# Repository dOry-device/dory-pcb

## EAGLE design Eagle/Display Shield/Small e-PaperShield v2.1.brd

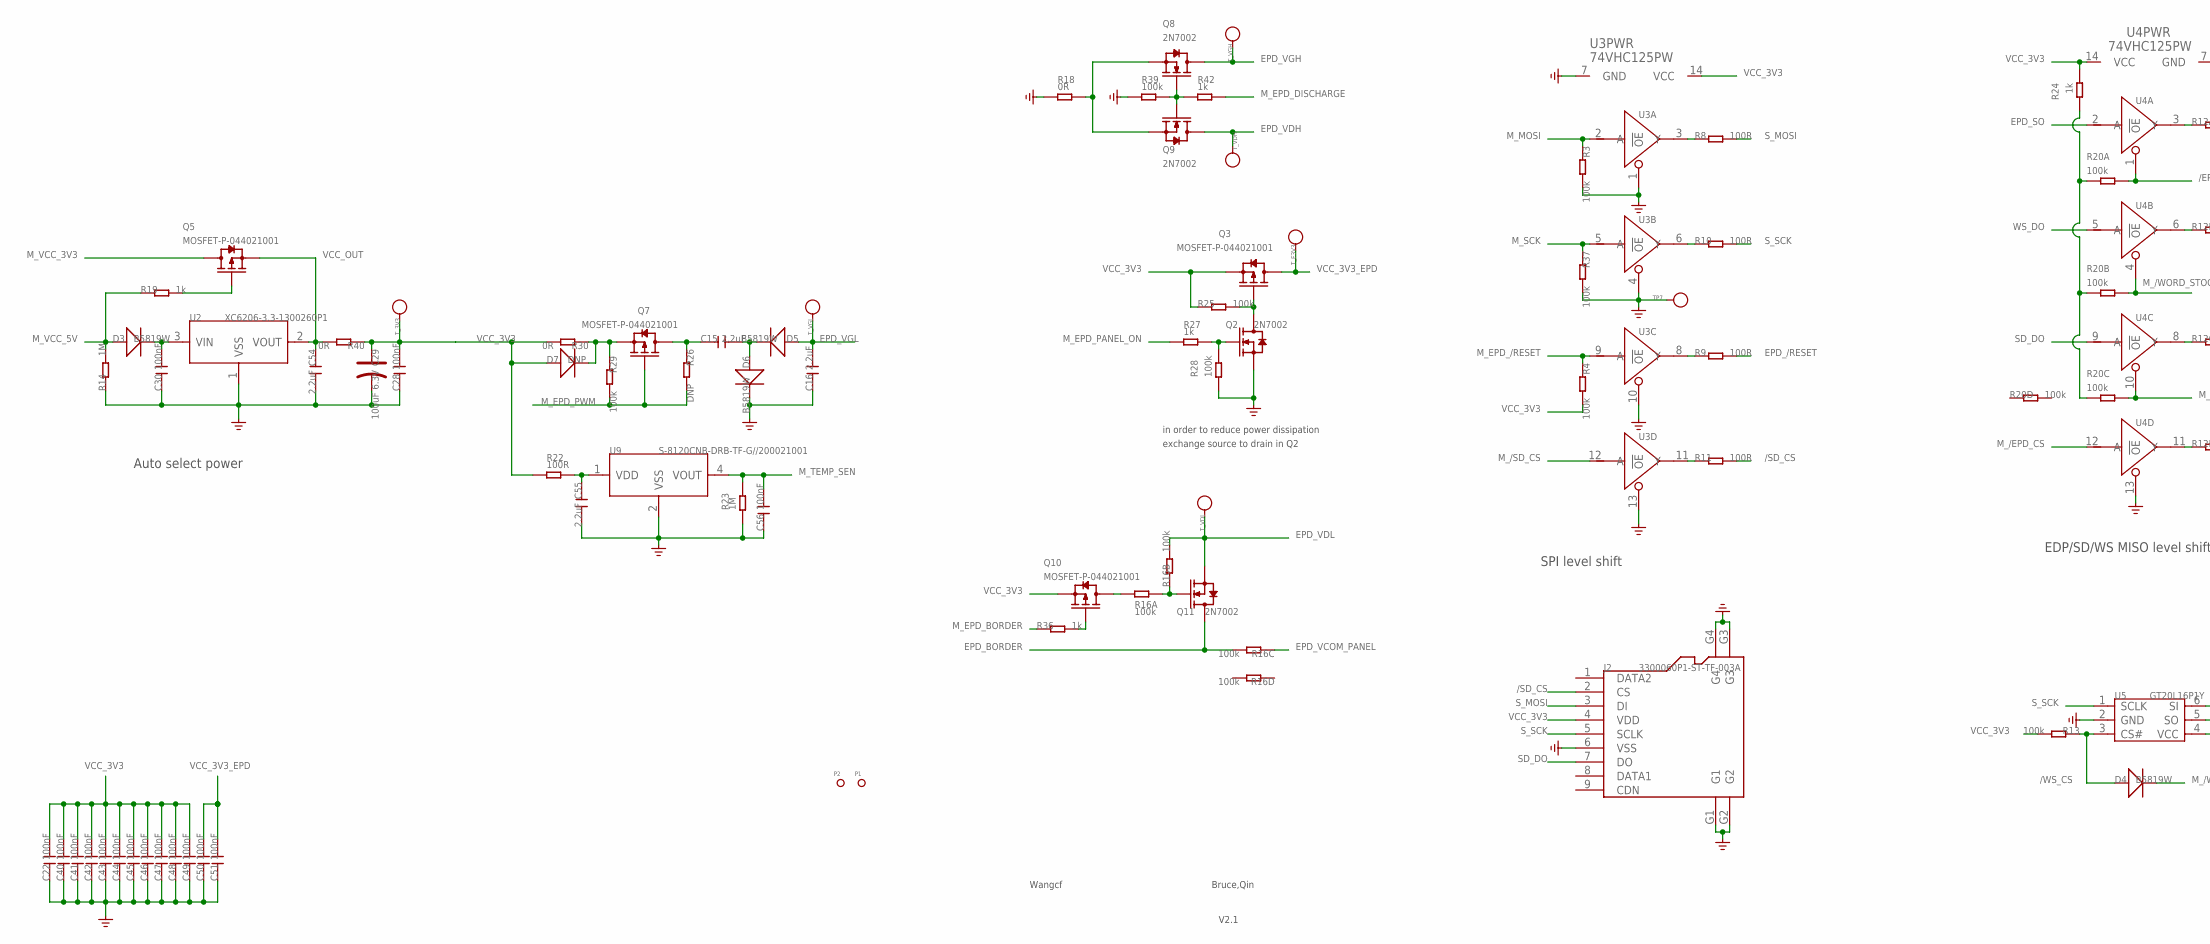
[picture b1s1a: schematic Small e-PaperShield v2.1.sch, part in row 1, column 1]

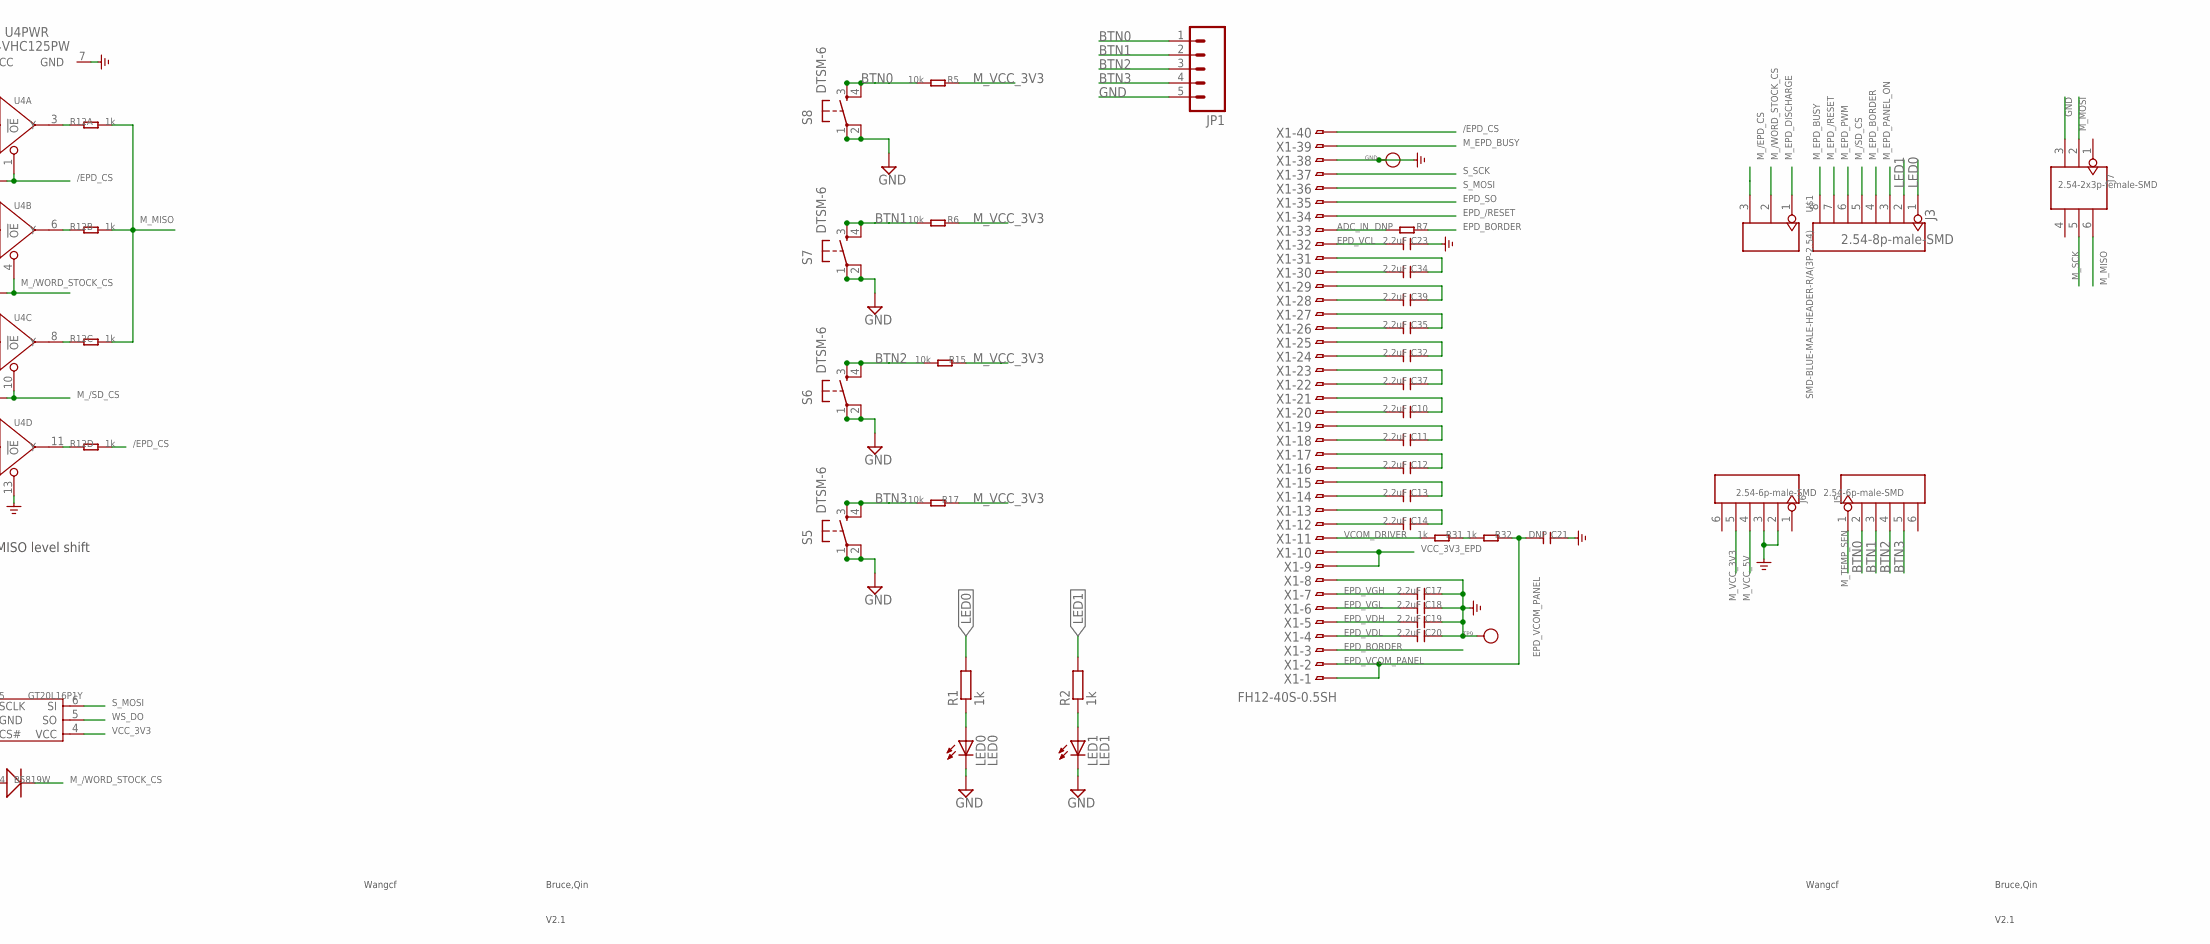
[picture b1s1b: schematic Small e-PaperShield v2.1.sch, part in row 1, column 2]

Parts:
C10, C11, C12, C13, C14, C15, C16, C17, C18, C19, C20, C23, C32, C34, C35, C37, C39, C54, C55: 2.2uF; C0805
C21: DNP; C0805
C22, C28, C30, C40, C41, C42, C43, C44, C45, C46, C47, C48, C49, C50, C51, C56: 100nF; C0603
C29: 100uF 6.3V; AVX-B
D3, D4, D5, D6: B5819W; SOD123
D7: DNP; SOD123
GND: PAD-TEST-POINT'3535'; TP_3535
J2: 3300060P1-ST-TF-003A; 9P-SMD-W/-RING
J3: 2.54-8p-male-SMD; 8P-2.54-SMD
J5, J6: 2.54-6p-male-SMD; 6P-2.54-SMD
J7: 2.54-2x3p-female-SMD; 2X3P-2.54-SMD
JP1: M05PTH_LONGPADS; 1X05_LONGPADS
LED0: LED0; CHIPLED_0603
LED1: LED1; CHIPLED_0603
P1, P2: PAD-MARK; ROUND-MARK-1.0
Q2, Q8, Q9, Q11: 2N7002; SOT23
Q3, Q5, Q7, Q10: MOSFET-P-044021001; SOT23
R1, R2, R19, R24, R27, R31, R32, R36, R42: 1k; R0603
R3, R4, R13, R25, R28, R29, R37, R39: 100k; R0603
R5, R6, R15, R17: 10k; R0603
R7, R26: DNP; R0603
R8, R9, R10, R11, R22: 100R; R0603
R12: 1k; 1206-8-3.3X2.4
R14, R23: 1M; R0603
R16, R20: 100k; 1206-8-3.3X2.4
R18, R30, R40: 0R; R0603
S5, S6, S7, S8: DTSM-6
TP7, TP9: PAD-TEST-POINT'3535'; TP_3535
T_3V3: PAD-TEST-POINT'3535'; TP_3535
T_E3V3: PAD-TEST-POINT'3535'; TP_3535
T_VDH: PAD-TEST-POINT'3535'; TP_3535
T_VDL: PAD-TEST-POINT'3535'; TP_3535
T_VGH: PAD-TEST-POINT'3535'; TP_3535
T_VGL: PAD-TEST-POINT'3535'; TP_3535
U2: XC6206-3.3-1300260P1; SOT23
U3, U4: 74VHC125PW; TSSOP14
U5: GT20L16P1Y; SOT23-6
U9: S-8120CNB-DRB-TF-G//200021001; SC-82AB
U$1: SMD-BLUE-MALE-HEADER-R/A(3P-2.54); H3-SMD-2.54
X1: FH12-40S-0.5SH

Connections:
3V3_LOG: R20.1, R20.2 (1), R20.3 (1), R24.2
/EPD_CS: R12.5 (2), R20.8 (2), U4.1 (!OE), X1.40
/SD_CS: J2.2 (CS), R11.2
/WS_CS: D4.+, R13.1, U5.3 (CS#)
ADC_IN: R7.2, X1.33
BTN0: J5.2, JP1.1, R5.2, S8.3, S8.4
BTN1: J5.3, JP1.2, R6.2, S7.3, S7.4
BTN2: J5.4, JP1.3, R15.2, S6.3, S6.4
BTN3: J5.5, JP1.4, R17.2, S5.3, S5.4
EPD_/RESET: R9.2, X1.34
EPD_BORDER: Q11.3 (D), R7.1, R16.6 (2), X1.3
EPD_SO: U4.2 (A), X1.35
EPD_VCL: C23.2, X1.32
EPD_VCOM_PANEL: C21.2, R16.3 (1), R32.1, X1.1, X1.2
EPD_VDH: C19.2, Q9.3 (D), T_VDH.T, X1.5
EPD_VDL: C20.2, Q11.2 (S), R16.7 (2), T_VDL.T, X1.4
EPD_VGH: C17.2, Q8.3 (D), T_VGH.T, X1.7
EPD_VGL: C16.2, C18.2, D5.+, T_VGL.T, X1.6
GND: C16.1, C17.1, C18.1, C19.1, C20.1, C21.1, C22.1, C23.1, C28.1, C29.-, C30.1, C40.1, C41.1, C42.1, C43.1, C44.1, C45.1, C46.1, C47.1, C48.1, C49.1, C50.1, C51.1, C54.2, C55.2, C56.1, D6.-, GND.T, J2.6 (VSS), J2.G1, J2.G2, J2.G3, J2.G4, J6.2, J6.3, J7.3, JP1.5, LED0.C, LED1.C, Q2.2 (S), R3.2, R14.1, R18.1, R23.1, R28.1, R37.2, R39.1, S5.1, S5.2, S6.1, S6.2, S7.1, S7.2, S8.1, S8.2, TP7.T, TP9.T, U2.1 (VSS), U3.1 (!OE), U3.4 (!OE), U3.7 (GND), U3.10 (!OE), U3.13 (!OE), U4.7 (GND), U4.13 (!OE), U5.2 (GND), U9.2 (VSS), X1.8, X1.38
LED0: J3.1, R1.2
LED1: J3.2, R2.2
M_/EPD_CS: U4.12 (A), U$1.3
M_/SD_CS: J3.5, R20.6 (2), U3.12 (A), U4.10 (!OE)
M_/WORD_STOCK_CS: D4.-, R20.7 (2), U4.4 (!OE), U$1.2
M_EPD_/RESET: J3.7, R4.1, U3.9 (A)
M_EPD_BORDER: J3.4, R36.1
M_EPD_BUSY: J3.8, X1.39
M_EPD_DISCHARGE: R42.2, U$1.1
M_EPD_PANEL_ON: J3.3, R27.1
M_EPD_PWM: J3.6, Q7.1 (G), R26.2, R29.2
M_MISO: J7.6, R12.6 (2), R12.7 (2), R12.8 (2)
M_MOSI: J7.2, R3.1, U3.2 (A)
M_SCK: J7.5, R37.1, U3.5 (A)
M_TEMP_SEN: C56.2, J5.1, R23.2, U9.4 (VOUT)
M_VCC_3V3: J6.5, Q5.3 (D), R5.1, R6.1, R15.1, R17.1
M_VCC_5V: D3.+, J6.4, R14.2, R19.1
unnamed: LED0.A, R1.1
unnamed: Q5.1 (G), R19.2
unnamed: C15.2, D5.-, D6.+
unnamed: D7.-, Q7.2 (S), R29.1, R30.1
unnamed: Q2.1 (G), R27.2, R28.2
unnamed: R11.1, U3.11 (Y)
unnamed: C30.2, D3.-, U2.3 (VIN)
unnamed: C15.1, Q7.3 (D), R26.1
unnamed: Q8.1 (G), Q9.1 (G), R39.2, R42.1
unnamed: Q2.3 (D), Q3.1 (G), R25.2
unnamed: R31.1, R32.2
unnamed: Q10.3 (D), R16.1
unnamed: Q10.1 (G), R36.2
unnamed: Q8.2 (S), Q9.2 (S), R18.2
unnamed: LED1.A, R2.1
unnamed: R12.1, U4.3 (Y)
unnamed: R12.2 (1), U4.6 (Y)
unnamed: R12.3 (1), U4.8 (Y)
unnamed: R12.4 (1), U4.11 (Y)
unnamed: Q11.1 (G), R16.2 (1), R16.8 (2)
unnamed: C34.1, X1.31
unnamed: C34.2, X1.30
unnamed: C39.1, X1.29
unnamed: C39.2, X1.28
unnamed: R8.1, U3.3 (Y)
unnamed: R10.1, U3.6 (Y)
unnamed: R9.1, U3.8 (Y)
unnamed: C35.1, X1.27
unnamed: C35.2, X1.26
unnamed: C32.1, X1.25
unnamed: C32.2, X1.24
unnamed: C37.1, X1.23
unnamed: C37.2, X1.22
unnamed: C10.1, X1.21
unnamed: C10.2, X1.20
unnamed: C11.1, X1.19
unnamed: C11.2, X1.18
unnamed: C12.1, X1.17
unnamed: C12.2, X1.16
unnamed: C13.1, X1.15
unnamed: C13.2, X1.14
unnamed: C14.1, X1.13
unnamed: C14.2, X1.12
SD_DO: J2.7 (DO), U4.9 (A)
S_MOSI: J2.3 (DI), R8.2, U5.6 (SI), X1.36
S_SCK: J2.5 (SCLK), R10.2, U5.1 (SCLK), X1.37
VCC_3V3: C22.2, C28.2, C29.+, C40.2, C41.2, C42.2, C43.2, C44.2, C45.2, C46.2, C47.2, C48.2, C49.2, D7.+, J2.4 (VDD), Q3.2 (S), Q10.2 (S), R4.2, R13.2, R22.1, R24.1, R25.1, R30.2, R40.1, T_3V3.T, U3.14 (VCC), U4.14 (VCC), U5.4 (VCC)
VCC_3V3_EPD: C50.2, C51.2, Q3.3 (D), T_E3V3.T, X1.9, X1.10
VCC_OUT: C54.1, Q5.2 (S), R40.2, U2.2 (VOUT)
VCOM_DRIVER: R31.2, X1.11
VDD: C55.1, R22.2, U9.1 (VDD)
WS_DO: U4.5 (A), U5.5 (SO)

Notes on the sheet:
EDP/SD/WS MISO level shift
SPI level shift
Auto select power
Bruce,Qin
V2.1
Wangcf
in order to reduce power dissipation
exchange source to drain in Q2

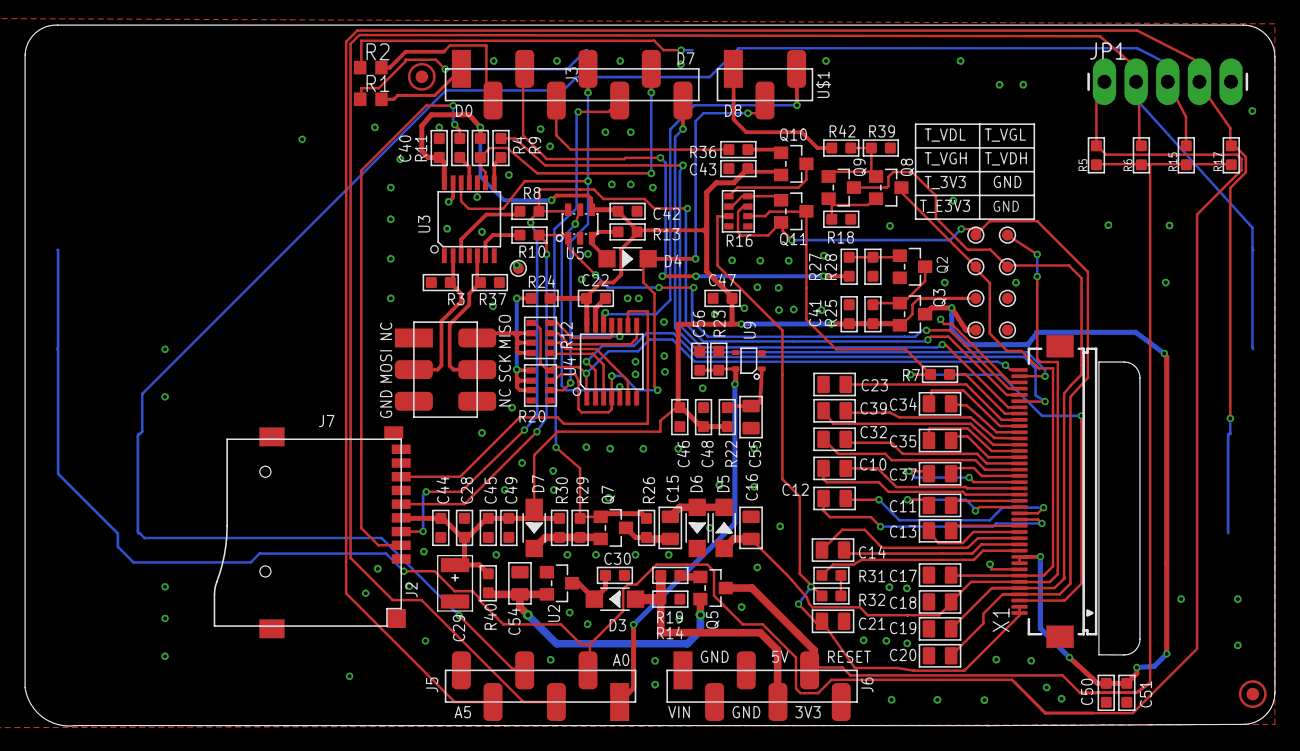
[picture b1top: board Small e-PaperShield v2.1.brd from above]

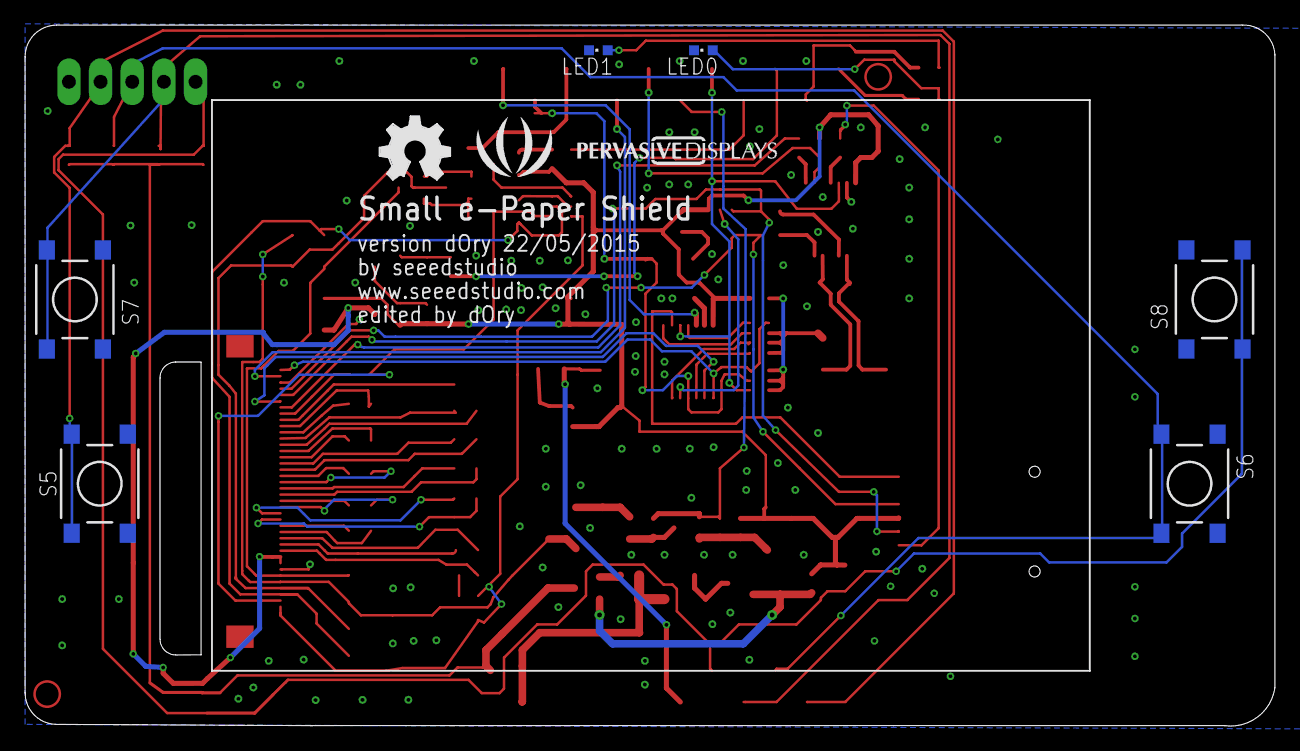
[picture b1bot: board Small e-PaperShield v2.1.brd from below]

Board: 2 copper layers, 100.3 x 56.2 mm, 118 parts (8 on the bottom side), 88 nets.

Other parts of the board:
U$20: LOGO_SILK
U$47: OSHW_FILLX200_NOTEXT

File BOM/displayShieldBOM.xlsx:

BOM Display shield
Qty | Value | Device | Seeed Part No. | Package | Parts | Description | Note
3 | 0R | R-0603 | 0010070P1 | R0603 | R18, R30, R40
5 | 100R | R-0603 | 301010090 | R0603 | R8, R9, R10, R11, R22
8 | 100k | R-0603 | 301010196 | R0603 | R3, R4, R13, R25, R28, R29, R37, R39
2 | 100k | R-4R-1206 | NA | 1206-8-3.3X2.4 | R16, R20 | Resistor Array
16 | 100nF | C-0603 | 0100020P1 | C0603 | C22, C28, C30, C40, C41, C42, C43, C44, C45, C46, C47, C48, C49, C50, C51, C56 | Ceramic Capacitors
1 | 100uF 6.3V | CAP-AVX-B | 302020015 | AVX-B | C29 | Electrolytic Capacitors,Tantalum Capacitors and Super Capacitors
4 | 10k | R-0603 | 0011240P1 | R0603 | R5, R6, R15, R17
2 | 1M | R-0603 | 301010151 | R0603 | R14, R23
9 | 1k | R-0603 | 0011090P1 | R0603 | R1, R2,R19, R24, R27, R31, R32, R36, R42
1 | 1k | R-4R-1206 | 301030012 | 1206-8-3.3X2.4 | R12 | Resistor Array
19 | 2.2uF | C-0805 | 302010148 | C0805 | C10, C11, C12, C13, C14, C15, C16, C17, C18, C19, C20, C23, C32, C34, C35, C37,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 | Ceramic Capacitors
1 | 2.54-2x3p-male-SMD | HEADER-2X3P-SMD | 320020119 | 2X3P-2.54-SMD | J7 |  | Part not available on OPL, but 2x5 can be cut manually and hand-soldered.
2 | 2.54-6p-male-SMD | HEADER-6P-SMD | 320020023 | 6P-2.54-SMD | J5, J6
1 | 2.54-3p-male-SMD | HEADER-3P-2.54-SMD | 320020023 | 8P-2.54-SMD | J3, J4 |  | Part not available on OPL, but 6P can be cut manually and hand-soldered.
1 | 2.54-8p-male-SMD | HEADER-8P-2.54-SMD | 320020024 | 8P-2.54-SMD | J3, J4
4 | 2N7002 | MOSFET-N'SOT23' | NA | SOT23 | Q2, Q8, Q9, Q11 | IRLL014:
1 | 3300060P1-ST-TF-003A | 3300060P1-ST-TF-003A | 320090000 | 9P-SMD-W/-RING | J2 | Micro SD Card
2 | 74VHC125PW | 74VHC125PW | 310050042 | TSSOP14 | U3, U4 | Quad Buffer/Line Driver;3-state
4 | B5819W | D'1206' | 304020034 | SOD123 | D3, D4, D5, D6
1 | DNP | C-0805 | - | C0805 | C21 | Ceramic Capacitors | Do not solder
1 | DNP | D'1206' | - | SOD123 | D7 |  | Do not solder
2 | DNP | R-0603 | - | R0603 | R7, R26 |  | Do not solder
4 | DTSM-6 | DTSM-6 | 311020004 | DTSM-6 | S5, S6, S7, S8 |  | Do not solder, only for reference if we dont find the external buttons.
1 | FH12-40S-0.5SH | FH12-40S-0.5SH | NA | FH12-40S-0.5SH | X1 | 0.5mm Pitch Connectors For FPC/FFC
1 | GT20L16P1Y | GT20L16P1Y | 310990002 | SOT23-6 | U5
1 | LED0 | LEDCHIPLED_0603 | 304090042 | CHIPLED_0603 | LED0 | LED
1 | LED1 | LEDCHIPLED_0603 | 304090043 | CHIPLED_0603 | LED1 | LED
4 | MOSFET-P-044021001 | MOSFET-P-044021001 | 305030014 | SOT23 | Q3, Q5, Q7, Q10 | CJ2305：SMD MOSFET P-CH 8V-4.1A
1 | DNP | S-8110C/8120C | - | SC-82AB | U9 | COMS Temperature Sensor IC | Do not solder
1 | XC6206-3.3-1300260P1 | XC6206-3.3-1300260P1 | 310030099 | SOT23 | U2 | LOW ESR Cap.Compatible Positive Voltage Regulators

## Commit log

2015-04-25 added footprint of jack connector - 5 pins
2015-04-25 correctd jack pinmap, removed spi series resistors.
2015-04-29 corrections in schematic according to Alex' feedback. (note, git client unavailable in windows - doing this from my mac)
2015-04-29 recalculated resistor values for charge circuit
2015-04-29 re annotated schematics
2015-04-29 xbee footprint incl 3d model ready
2015-04-29 pcb board shape defined, gps bee 3d model
2015-04-30 SET ORIGIN IN CENTER OF PCB, adjusted center position of screen. completed display 3d model, corrected pin locations.
2015-04-30 no compile errors left
2015-05-01 exported 3d pcb model
2015-05-19 corrected Schematic
2015-05-19 added display shield files
2015-05-19 removed all unnecessary components of display shield
2015-05-19 re-placed components to board area, added 40pin connector. ready to go
2015-05-19 reshaped board, snapped components to grid.
2015-05-19 re-routed most of the traces
2015-05-26 DRC corrections for display shield
2015-05-26 uptdated display shield component in mainboard
2015-05-26 updated gitignore
2015-05-26 added pull-ups for buttons on display shield
2015-05-26 placed components, corrected some errors on schematics
2015-05-26 removed unused files. added seeed design rules
2015-05-27 resized display shield, placed buttons and leds to their final position
2015-06-01 created BOM and adapted schematics to part list from Seeed
2015-06-01 autorouted missing connecitons
2015-06-03 changed PCB shape, replaced components to Seeed parts, created bom, added power switch circuit
2015-06-06 new battery charger on mainboard, added power switch, tiltet zigbee. Added conductivity sensor board
2015-06-07 defined nets and DRU
2015-06-07 placed power componenets
2015-06-07 finished component placing
2015-06-07 new jack connector. better 3d models
2015-06-08 changed diodes in conductivity sensor
2015-06-08 added conductivity spice files
2015-06-09 routing mainboard almost done
2015-06-10 added ground plane
2015-06-10 connected ground plane
2015-06-10 reordered designators
2015-06-12 DRU mainboard. placed components conductivity sensor
2015-06-16 rerouted all power traces. generated output pdfs
2015-06-24 finished conductivity and turbidity sensors
2015-06-24 finished display shield
2015-06-30 new pcb shape
2015-07-01 definite board shape
2015-07-02 created gerber files for mainboard and conductivity
2015-07-02 final gerber files for display shield
2015-07-02 added logos to pcbs
2015-07-02 finished all PCBs with logos
2015-07-03 corrected pcbs according to comments from Seeed.
2015-07-03 generated 3d models

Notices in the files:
parts and their libraries:
SparkFun-Connectors: Licensing: Creative Commons ShareAlike 4.0 International - https://creativecommons.org/licenses/by-sa/4.0
